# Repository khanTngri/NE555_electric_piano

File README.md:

# NE555_electric_piano
Simple electric piano based on NE555 IC

Open full schematic (PDF)](NE555_electric_paino/piano.pdf)

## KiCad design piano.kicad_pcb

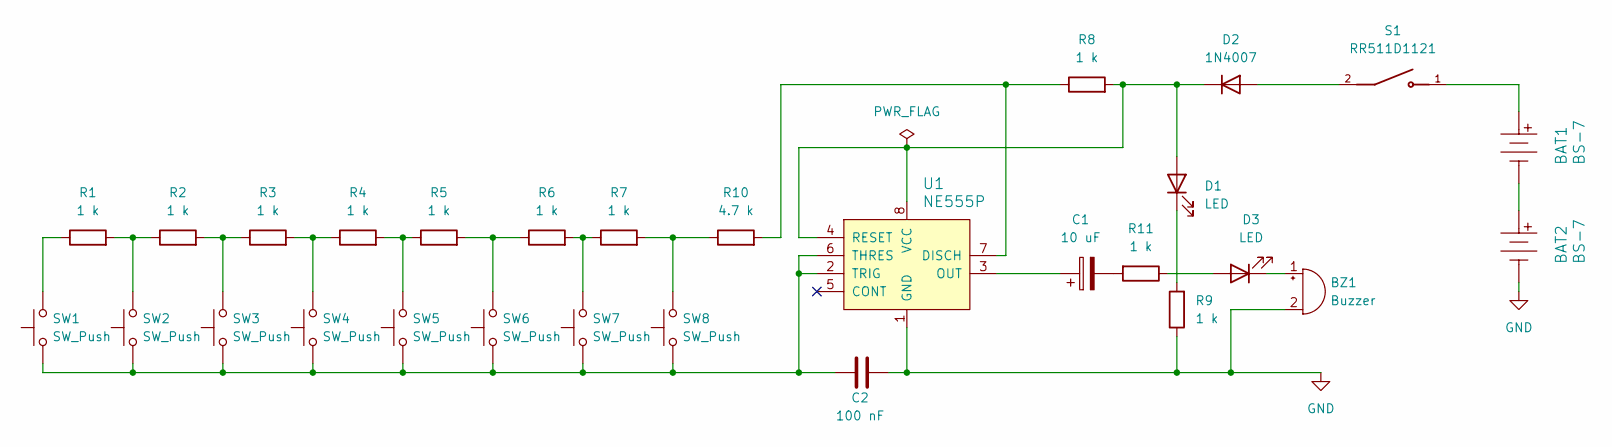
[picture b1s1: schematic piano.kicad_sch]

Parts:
BAT1, BAT2: BS-7; Battery_Holder_Coin_2032_BS-7; MPN BS-7; Digi-Key_PN BS-7-ND
BZ1: Buzzer; Buzzer_12x9.5RM7.6
C1: 10 uF; CP_Radial_D4.0mm_P1.50mm
C2: 100 nF; C_Disc_D3.0mm_W1.6mm_P2.50mm
D1, D3: LED; LED_D3.0mm
D2: 1N4007; D_DO-41_SOD81_P10.16mm_Horizontal
R1, R2, R3, R4, R5, R6, R7, R8, R9, R11: 1 k; R_Axial_DIN0617_L17.0mm_D6.0mm_P30.48mm_Horizontal
R10: 4.7 k; R_Axial_DIN0617_L17.0mm_D6.0mm_P30.48mm_Horizontal
S1: RR511D1121; E-SWITCH_RR511D1121; PARTREV A
SW1, SW2, SW3, SW4, SW5, SW6, SW7, SW8: SW_Push; SW_Push_1P1T_NO_CK_PTS125Sx85PSMTR
U1: NE555P; DIP-8_W7.62mm; MPN NE555P; Digi-Key_PN 296-1411-5-ND

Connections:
GND: BAT2.Neg, BZ1.2 (-), C2.2, R9.1, U1.1 (GND)
unnamed: BAT1.Neg, BAT2.Pos
unnamed: BAT1.Pos, S1.1
unnamed: BZ1.1 (+), D3.1 (K)
unnamed: C1.2, R11.2
unnamed: D1.2 (A), D2.1 (K), R8.2, U1.4 (RESET), U1.8 (VCC)
unnamed: D1.1 (K), R9.2
unnamed: D2.2 (A), S1.2
unnamed: D3.2 (A), R11.1
unnamed: R1.1, SW1.2
unnamed: R1.2, R2.1, SW2.2
unnamed: R2.2, R3.1, SW3.2
unnamed: R3.2, R4.1, SW4.2
unnamed: R4.2, R5.1, SW5.2
unnamed: R5.2, R6.1, SW6.2
unnamed: R6.2, R7.1, SW7.2
unnamed: R7.2, R10.1, SW8.2
unnamed: R8.1, R10.2, U1.7 (DISCH)
unnamed: C1.1, U1.3 (OUT)
unnamed: C2.1, SW1.1, SW2.1, SW3.1, SW4.1, SW5.1, SW6.1, SW7.1, SW8.1, U1.2 (TRIG), U1.6 (THRES)

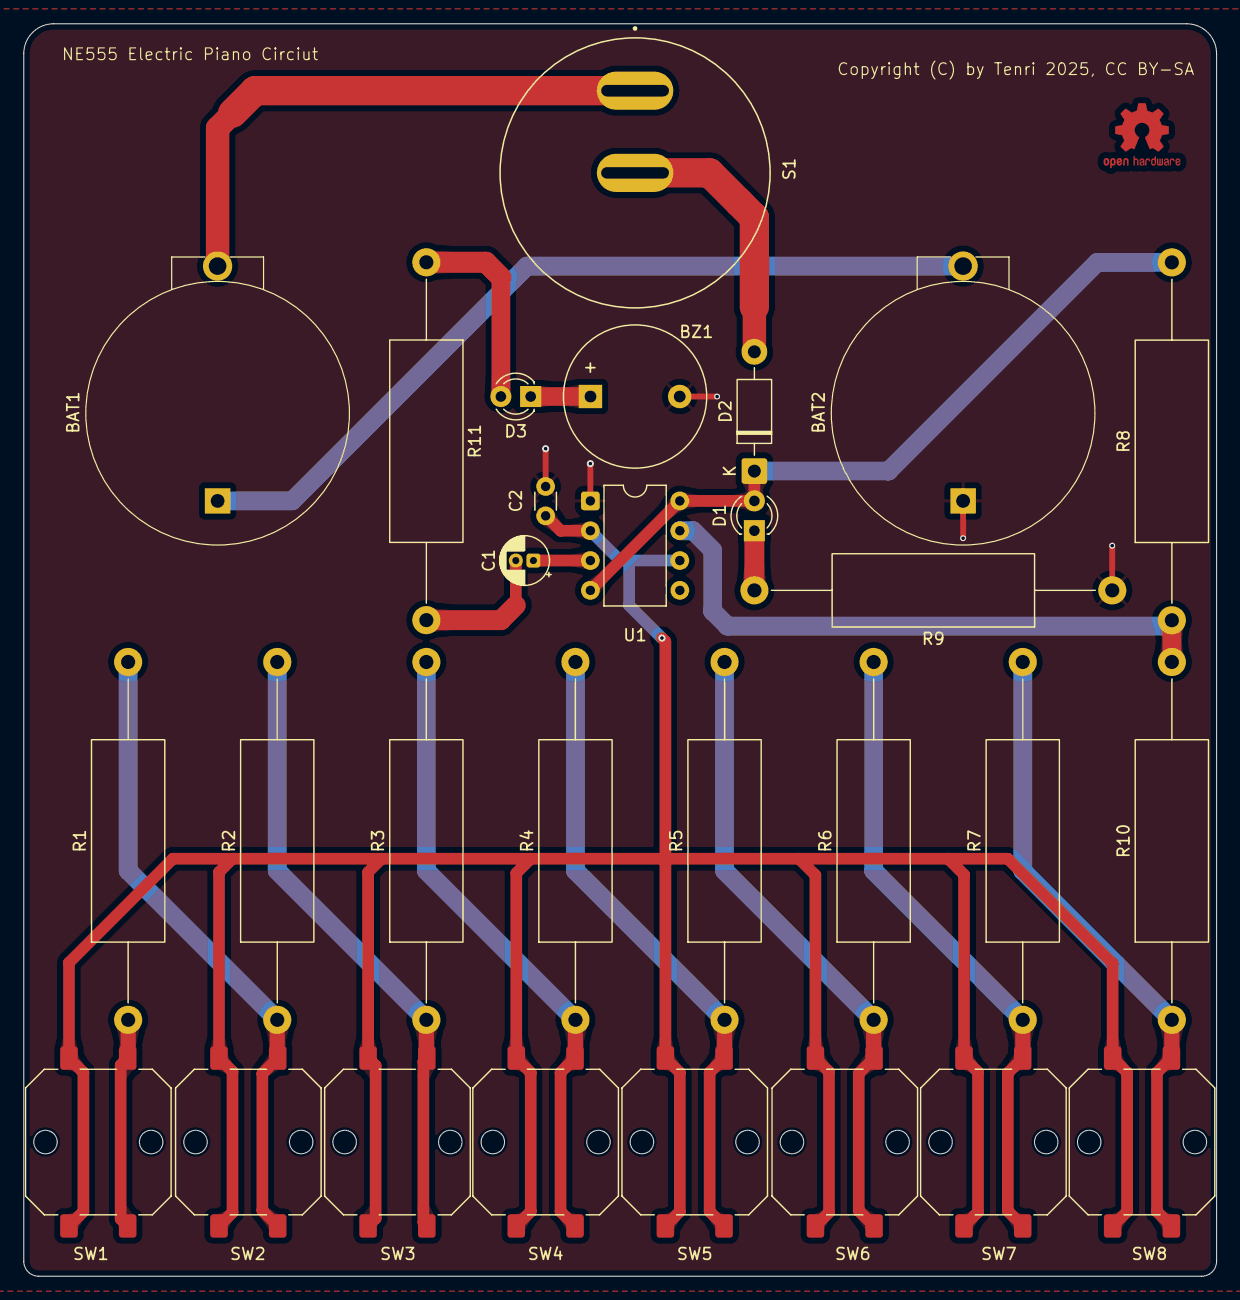
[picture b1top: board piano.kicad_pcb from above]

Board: 2 copper layers, 101.6 x 106.7 mm, 29 parts (0 on the bottom side), 20 nets.

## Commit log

2025-12-17 Initial KiCad piano project
2025-12-17 Add new files to NE555 piano project

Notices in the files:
piano.kicad_pcb:
Copyright (C) by Tenri 2025, CC BY-SA
